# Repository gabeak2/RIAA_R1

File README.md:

RIAA Preamp for MM cartridge, copied out of Douglas Self's book with minor modifications. Powered directly off mains (obviously with xfmr and linear regs) so yeah don't make this or use it or even think about it.

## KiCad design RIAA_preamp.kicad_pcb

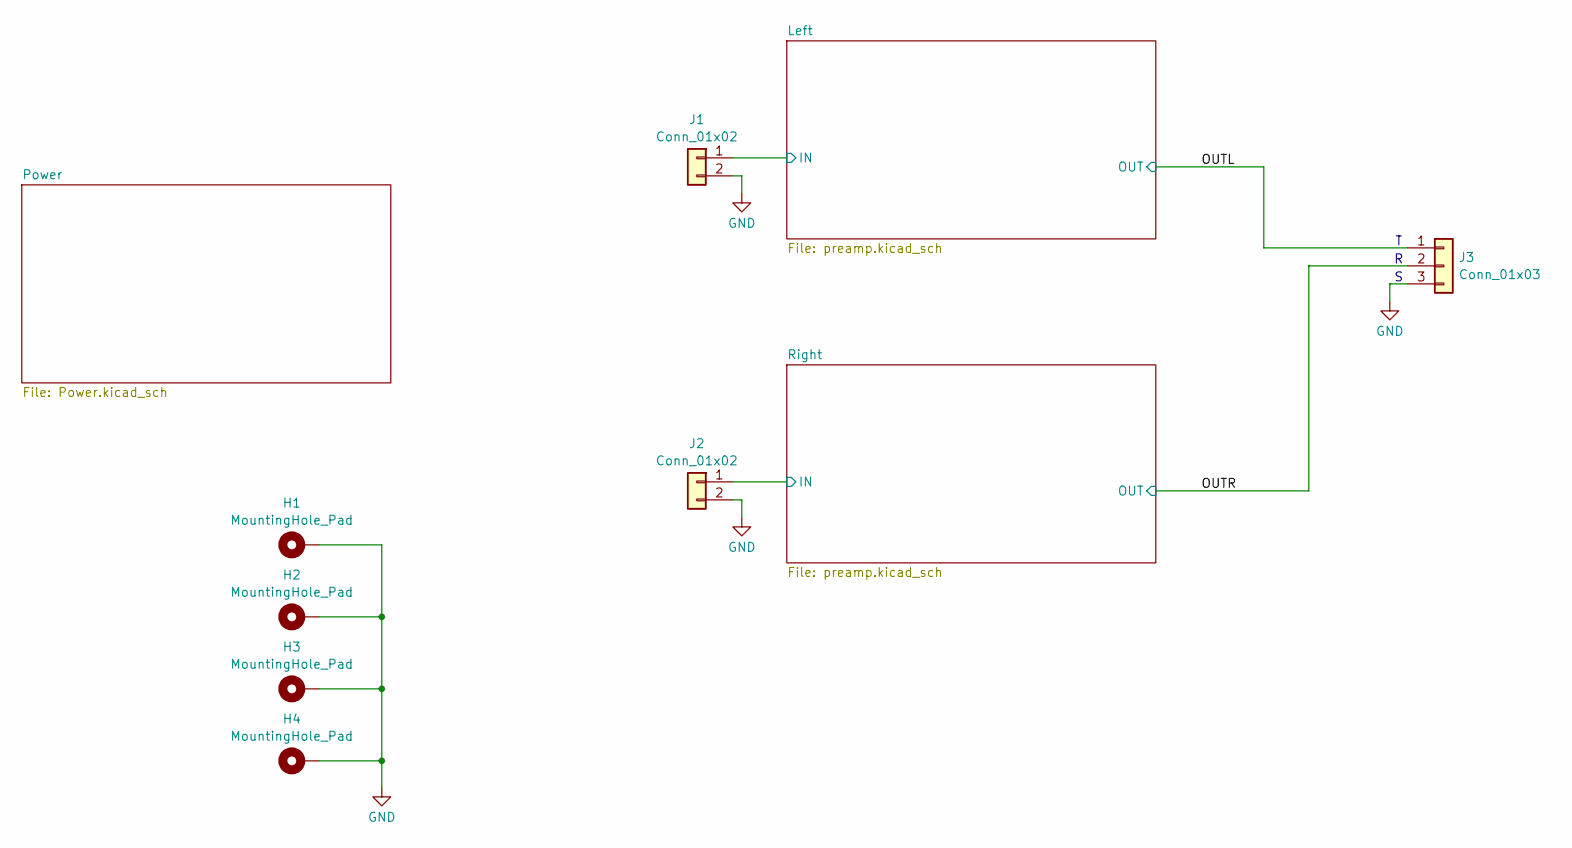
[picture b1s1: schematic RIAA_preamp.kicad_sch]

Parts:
H1, H2, H3, H4: MountingHole_Pad; MountingHole_3.2mm_M3_DIN965_Pad
J1, J2: Conn_01x02; PinHeader_1x02_P2.54mm_Vertical
J3: Conn_01x03; PinHeader_1x03_P2.54mm_Vertical

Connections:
/Left/IN: J1.1; also elsewhere on the board
/OUTL: J3.1; also elsewhere on the board
/OUTR: J3.2; also elsewhere on the board
/Right/IN: J2.1; also elsewhere on the board
GND: H1.1, H2.1, H3.1, H4.1, J1.2, J2.2, J3.3; also elsewhere on the board

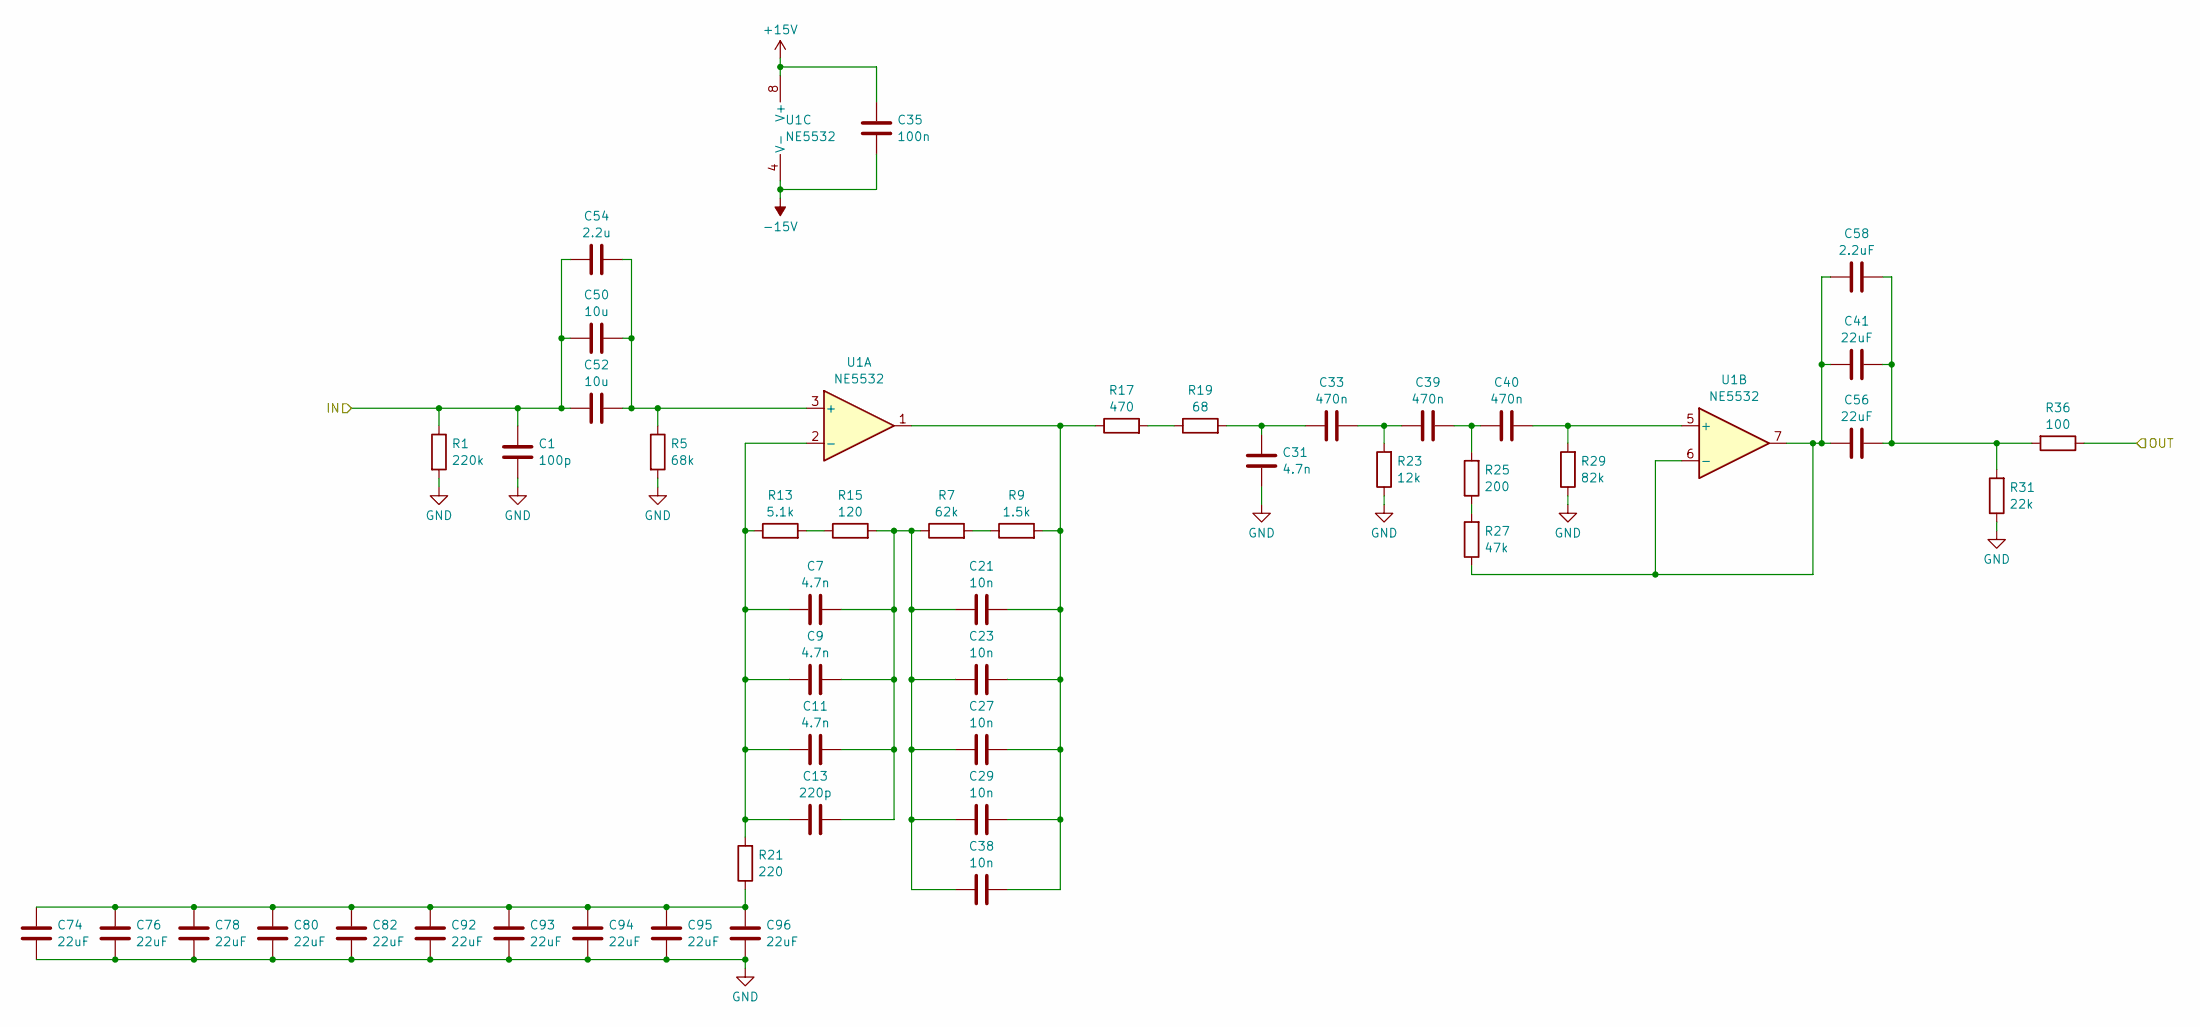
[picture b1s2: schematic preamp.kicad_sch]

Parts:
C1: 100p; C_0603_1608Metric; LCSC C55722
C7, C9, C11, C31: 4.7n; C_0603_1608Metric; LCSC C883564
C13: 220p; C_0603_1608Metric; LCSC C519500
C21, C23, C27, C29, C38: 10n; C_0805_2012Metric; LCSC C441760
C33, C39, C40: 470n; C_0805_2012Metric; LCSC C13967
C35: 100n; C_0603_1608Metric; LCSC C14663
C41, C56: 22uF; C_0805_2012Metric; LCSC C45783
C50, C52: 10u; C_0805_2012Metric; LCSC C440198
C54: 2.2u; C_0805_2012Metric; LCSC C377773
C58: 2.2uF; C_0805_2012Metric; LCSC C377773
C74, C76, C78, C80, C82, C92, C93, C94, C95, C96: 22uF; C_0603_1608Metric; LCSC C59461
R1: 220k; R_0603_1608Metric; LCSC C22961
R5: 68k; R_0603_1608Metric; LCSC C23231
R7: 62k; R_0603_1608Metric; LCSC C23221
R9: 1.5k; R_0603_1608Metric; LCSC C22843
R13: 5.1k; R_0603_1608Metric; LCSC C23186
R15: 120; R_0603_1608Metric; LCSC C22787
R17: 470; R_0603_1608Metric; LCSC C23179
R19: 68; R_0603_1608Metric; LCSC C27592
R21: 220; R_0603_1608Metric; LCSC C22962
R23: 12k; R_0603_1608Metric; LCSC C22790
R25: 200; R_0603_1608Metric; LCSC C8218
R27: 47k; R_0603_1608Metric; LCSC C25819
R29: 82k; R_0603_1608Metric; LCSC C23254
R31: 22k; R_0603_1608Metric; LCSC C31850
R36: 100; R_0603_1608Metric; LCSC C22775
U1: NE5532; SOIC-8_3.9x4.9mm_P1.27mm; LCSC C7426

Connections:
+15V: C35.2, U1.8 (V+); also elsewhere on the board
-15V: C35.1, U1.4 (V-); also elsewhere on the board
/Left/IN: C1.1, C50.1, C52.1, C54.1, R1.1; also elsewhere on the board
/OUTL: R36.1; also elsewhere on the board
GND: C1.2, C31.1, C74.2, C76.2, C78.2, C80.2, C82.2, C92.2, C93.2, C94.2, C95.2, C96.2, R1.2, R5.2, R23.1, R29.1, R31.1; also elsewhere on the board
unnamed: C7.2, C9.2, C11.2, C13.2, C21.1, C23.1, C27.1, C29.1, C38.1, R7.1, R15.2
unnamed: C21.2, C23.2, C27.2, C29.2, C38.2, R9.2, R17.1, U1.1
unnamed: C31.2, C33.2, R19.2
unnamed: C33.1, C39.2, R23.2
unnamed: C39.1, C40.2, R25.2
unnamed: C41.1, C56.1, C58.1, R31.2, R36.2
unnamed: C74.1, C76.1, C78.1, C80.1, C82.1, C92.1, C93.1, C94.1, C95.1, C96.1, R21.1
unnamed: R7.2, R9.1
unnamed: R13.2, R15.1
unnamed: R17.2, R19.1
unnamed: R25.1, R27.2
unnamed: C50.2, C52.2, C54.2, R5.1, U1.3 (+)
unnamed: C7.1, C9.1, C11.1, C13.1, R13.1, R21.2, U1.2 (-)
unnamed: C40.1, R29.2, U1.5 (+)
unnamed: C41.2, C56.2, C58.2, R27.1, U1.6 (-), U1.7

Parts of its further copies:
C5: 100p; C_0603_1608Metric; LCSC C55722
C6, C8, C10, C22: 4.7n; C_0603_1608Metric; LCSC C883564
C12: 220p; C_0603_1608Metric; LCSC C519500
C17, C18, C19, C20, C36: 10n; C_0805_2012Metric; LCSC C441760
C24, C28, C30: 470n; C_0805_2012Metric; LCSC C13967
C32, C55: 22uF; C_0805_2012Metric; LCSC C45783
C34: 100n; C_0603_1608Metric; LCSC C14663
C49, C51: 10u; C_0805_2012Metric; LCSC C440198
C53: 2.2u; C_0805_2012Metric; LCSC C377773
C57: 2.2uF; C_0805_2012Metric; LCSC C377773
C73, C75, C77, C79, C81, C87, C88, C89, C90, C91: 22uF; C_0603_1608Metric; LCSC C59461
R3: 220k; R_0603_1608Metric; LCSC C22961
R4: 68k; R_0603_1608Metric; LCSC C23231
R6: 62k; R_0603_1608Metric; LCSC C23221
R8: 1.5k; R_0603_1608Metric; LCSC C22843
R11: 5.1k; R_0603_1608Metric; LCSC C23186
R12: 120; R_0603_1608Metric; LCSC C22787
R14: 470; R_0603_1608Metric; LCSC C23179
R16: 68; R_0603_1608Metric; LCSC C27592
R18: 12k; R_0603_1608Metric; LCSC C22790
R20: 220; R_0603_1608Metric; LCSC C22962
R22: 200; R_0603_1608Metric; LCSC C8218
R24: 47k; R_0603_1608Metric; LCSC C25819
R26: 82k; R_0603_1608Metric; LCSC C23254
R28: 22k; R_0603_1608Metric; LCSC C31850
R30: 100; R_0603_1608Metric; LCSC C22775
U5: NE5532; SOIC-8_3.9x4.9mm_P1.27mm; LCSC C7426

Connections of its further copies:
+15V: C34.2, U5.8 (V+); also elsewhere on the board
-15V: C34.1, U5.4 (V-); also elsewhere on the board
/OUTR: R30.1; also elsewhere on the board
/Right/IN: C5.1, C49.1, C51.1, C53.1, R3.1; also elsewhere on the board
GND: C5.2, C22.1, C73.2, C75.2, C77.2, C79.2, C81.2, C87.2, C88.2, C89.2, C90.2, C91.2, R3.2, R4.2, R18.1, R26.1, R28.1; also elsewhere on the board
unnamed: C6.2, C8.2, C10.2, C12.2, C17.1, C18.1, C19.1, C20.1, C36.1, R6.1, R12.2
unnamed: C17.2, C18.2, C19.2, C20.2, C36.2, R8.2, R14.1, U5.1
unnamed: C22.2, C24.2, R16.2
unnamed: C24.1, C28.2, R18.2
unnamed: C28.1, C30.2, R22.2
unnamed: C32.1, C55.1, C57.1, R28.2, R30.2
unnamed: C73.1, C75.1, C77.1, C79.1, C81.1, C87.1, C88.1, C89.1, C90.1, C91.1, R20.1
unnamed: R6.2, R8.1
unnamed: R11.2, R12.1
unnamed: R14.2, R16.1
unnamed: R22.1, R24.2
unnamed: C49.2, C51.2, C53.2, R4.1, U5.3 (+)
unnamed: C6.1, C8.1, C10.1, C12.1, R11.1, R20.2, U5.2 (-)
unnamed: C30.1, R26.2, U5.5 (+)
unnamed: C32.2, C55.2, C57.2, R24.1, U5.6 (-), U5.7

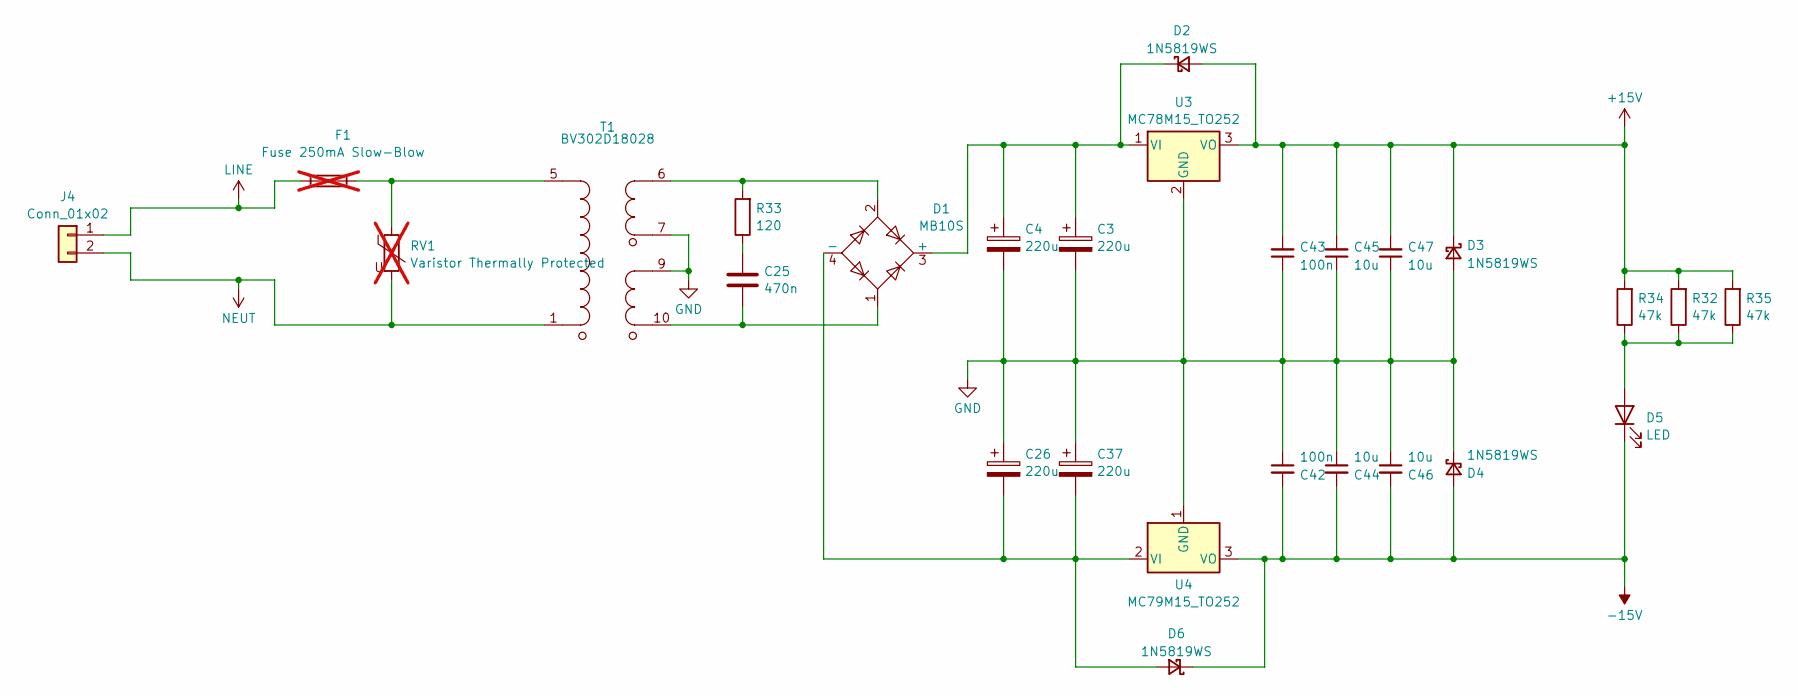
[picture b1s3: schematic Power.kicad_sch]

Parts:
C3, C4, C26, C37: 220u; CP_Elec_8x10.5; LCSC C2162304
C25: 470n; C_0805_2012Metric; LCSC C13967
C42, C43: 100n; C_0805_2012Metric; LCSC C14663
C44, C45, C46, C47: 10u; C_0805_2012Metric; LCSC C440198
D1: MB10S; TO-269AA; LCSC C2488
D2, D3, D4, D6: 1N5819WS; D_SOD-323; LCSC C191023
D5: LED; LED_D5.0mm
F1: Fuse 250mA Slow-Blow; Fuse_BelFuse_0ZRE0008FF_L8.3mm_W3.8mm; not fitted
J4: Conn_01x02; SolderWire-1sqmm_1x02_P5.4mm_D1.4mm_OD2.7mm_Relief
R32, R34, R35: 47k; R_0603_1608Metric; LCSC C25819
R33: 120; R_0603_1608Metric; LCSC C22787
RV1: Varistor Thermally Protected; RV_Disc_D12mm_W3.9mm_P7.5mm; not fitted
T1: BV302D18028
U3: MC78M15_TO252; TO-252-2; LCSC C95992
U4: MC79M15_TO252; TO-252-2; LCSC C19626424

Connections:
+15V: C43.2, C45.2, C47.2, D2.2 (A), D3.1 (K), R32.2, R34.2, R35.2, U3.3 (VO); also elsewhere on the board
-15V: C42.2, C44.2, C46.2, D4.2 (A), D5.1 (K), D6.1 (K), U4.3 (VO); also elsewhere on the board
GND: C3.2, C4.2, C26.1, C37.1, C42.1, C43.1, C44.1, C45.1, C46.1, C47.1, D3.2 (A), D4.1 (K), T1.7, T1.9, U3.2 (GND), U4.1 (GND); also elsewhere on the board
LINE: F1.1, J4.1
NEUT: J4.2, RV1.2, T1.1
unnamed: C25.1, R33.1
unnamed: C25.2, D1.1, T1.10
unnamed: C3.1, C4.1, D1.3 (+), D2.1 (K), U3.1 (VI)
unnamed: C26.2, C37.2, D1.4 (-), D6.2 (A), U4.2 (VI)
unnamed: D1.2, R33.2, T1.6
unnamed: D5.2 (A), R32.1, R34.1, R35.1
unnamed: F1.2, RV1.1, T1.5

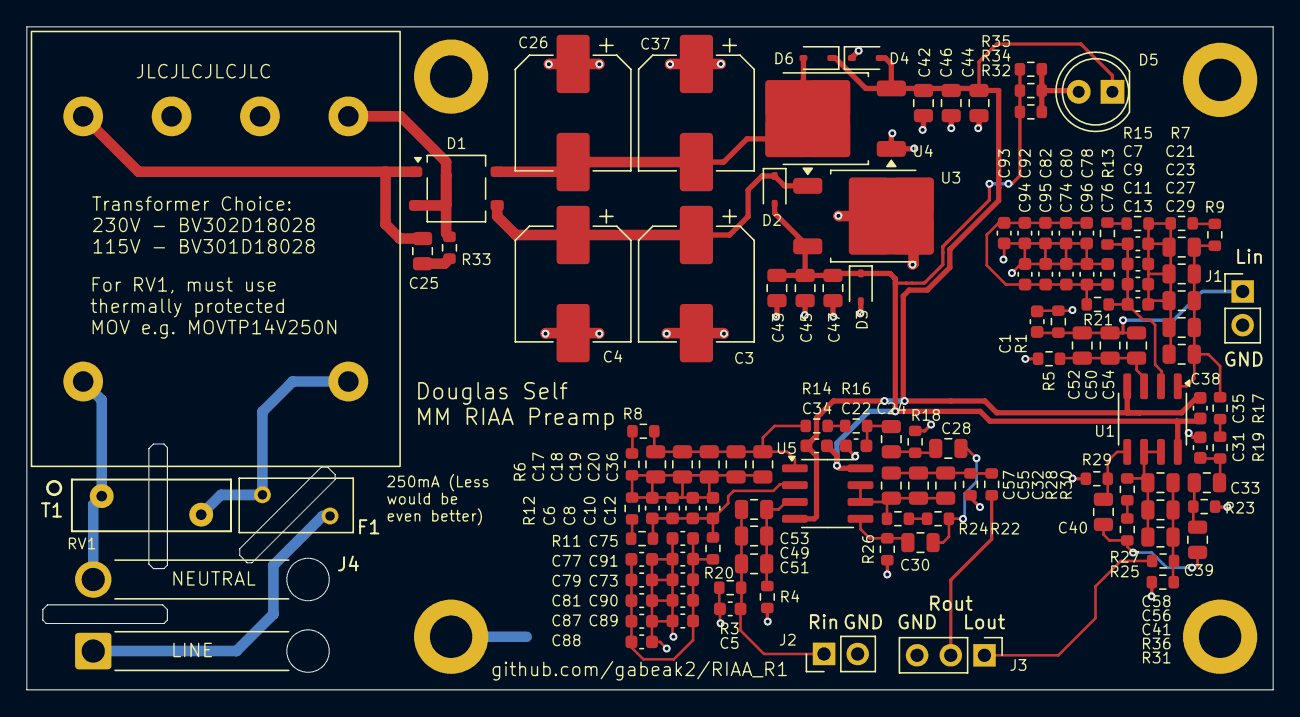
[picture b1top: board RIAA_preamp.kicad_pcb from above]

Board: 2 copper layers, 94.0 x 50.0 mm, 128 parts (0 on the bottom side), 46 nets.

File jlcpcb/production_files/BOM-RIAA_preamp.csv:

Comment,Designator,Footprint,LCSC,Quantity
470n,"C24,C25,C28,C30,C33,C39,C40",C_0805_2012Metric,C13967,7
100n,"C34,C35",C_0603_1608Metric,C14663,2
1N5819WS,"D2,D3,D4,D6",D_SOD-323,C191023,4
MC79M15_TO252,U4,TO-252-2,C19626424,1
220u,"C26,C3,C37,C4",CP_Elec_8x10.5,C2162304,4
100,"R30,R36",R_0603_1608Metric,C22775,2
120,"R12,R15,R33",R_0603_1608Metric,C22787,3
12k,"R18,R23",R_0603_1608Metric,C22790,2
1.5k,"R8,R9",R_0603_1608Metric,C22843,2
220k,"R1,R3",R_0603_1608Metric,C22961,2
220,"R20,R21",R_0603_1608Metric,C22962,2
470,"R14,R17",R_0603_1608Metric,C23179,2
5.1k,"R11,R13",R_0603_1608Metric,C23186,2
62k,"R6,R7",R_0603_1608Metric,C23221,2
68k,"R4,R5",R_0603_1608Metric,C23231,2
82k,"R26,R29",R_0603_1608Metric,C23254,2
MB10S,D1,TO-269AA,C2488,1
47k,"R24,R27,R32,R34,R35",R_0603_1608Metric,C25819,5
68,"R16,R19",R_0603_1608Metric,C27592,2
22k,"R28,R31",R_0603_1608Metric,C31850,2
2.2u,"C53,C54,C57,C58",C_0805_2012Metric,C377773,4
10u,"C44,C45,C46,C47,C49,C50,C51,C52",C_0805_2012Metric,C440198,8
10n,"C17,C18,C19,C20,C21,C23,C27,C29,C36,C38",C_0805_2012Metric,C441760,10
22uF,"C32,C41,C55,C56",C_0805_2012Metric,C45783,4
100n,"C42,C43",C_0805_2012Metric,C49678,2
220p,"C12,C13",C_0603_1608Metric,C519500,2
100p,"C1,C5",C_0603_1608Metric,C55722,2
22uF,"C73,C74,C75,C76,C77,C78,C79,C80,C81,C82,C87,C88,C89,C90,C91,C92,C93,C94,C95,C96",C_0603_1608Metric,C59461,20
NE5532,"U1,U5",SOIC-8_3.9x4.9mm_P1.27mm,C7426,2
200,"R22,R25",R_0603_1608Metric,C8218,2
4.7n,"C10,C11,C22,C31,C6,C7,C8,C9",C_0603_1608Metric,C883564,8
MC78M15_TO252,U3,TO-252-2,C95992,1
Conn_01x02,J4,SolderWire-1sqmm_1x02_P5.4mm_D1.4mm_OD2.7mm_Relief,,1
Conn_01x03,J3,PinHeader_1x03_P2.54mm_Vertical,,1
MountingHole_Pad,H2,MountingHole_3.2mm_M3_DIN965_Pad,,1
LED,D5,LED_D5.0mm,,1
MountingHole_Pad,H1,MountingHole_3.2mm_M3_DIN965_Pad,,1
MountingHole_Pad,H4,MountingHole_3.2mm_M3_DIN965_Pad,,1
MountingHole_Pad,H3,MountingHole_3.2mm_M3_DIN965_Pad,,1
Conn_01x02,J2,PinHeader_1x02_P2.54mm_Vertical,,1
BV302D18028,T1,BV302D18028,,1
Conn_01x02,J1,PinHeader_1x02_P2.54mm_Vertical,,1
